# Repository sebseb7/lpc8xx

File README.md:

lpc8xx_template
===============

template project with makefile, flash script and eval board.

- - - 

####lpc812 features:

* Cortex-M0+ Core
* 30 Mhz
* 16kb flash (lpc811: 8kb)
* 4kb RAM (lpc811: 2kb)
* USART Bootloader and SerialWireDebugging ( make debug )
* ROM drivers for USART, i2c and power profiles
* 14 hihgly configurable GPIO Pins (you can connect UART, I2C and SPI to any pin)
* 3 * USART , 2 * SPI , 1 * I2C
* internal RC with 1% accuracy
* while(1); @ 30 Mhz ==> 5.5mA

- - -

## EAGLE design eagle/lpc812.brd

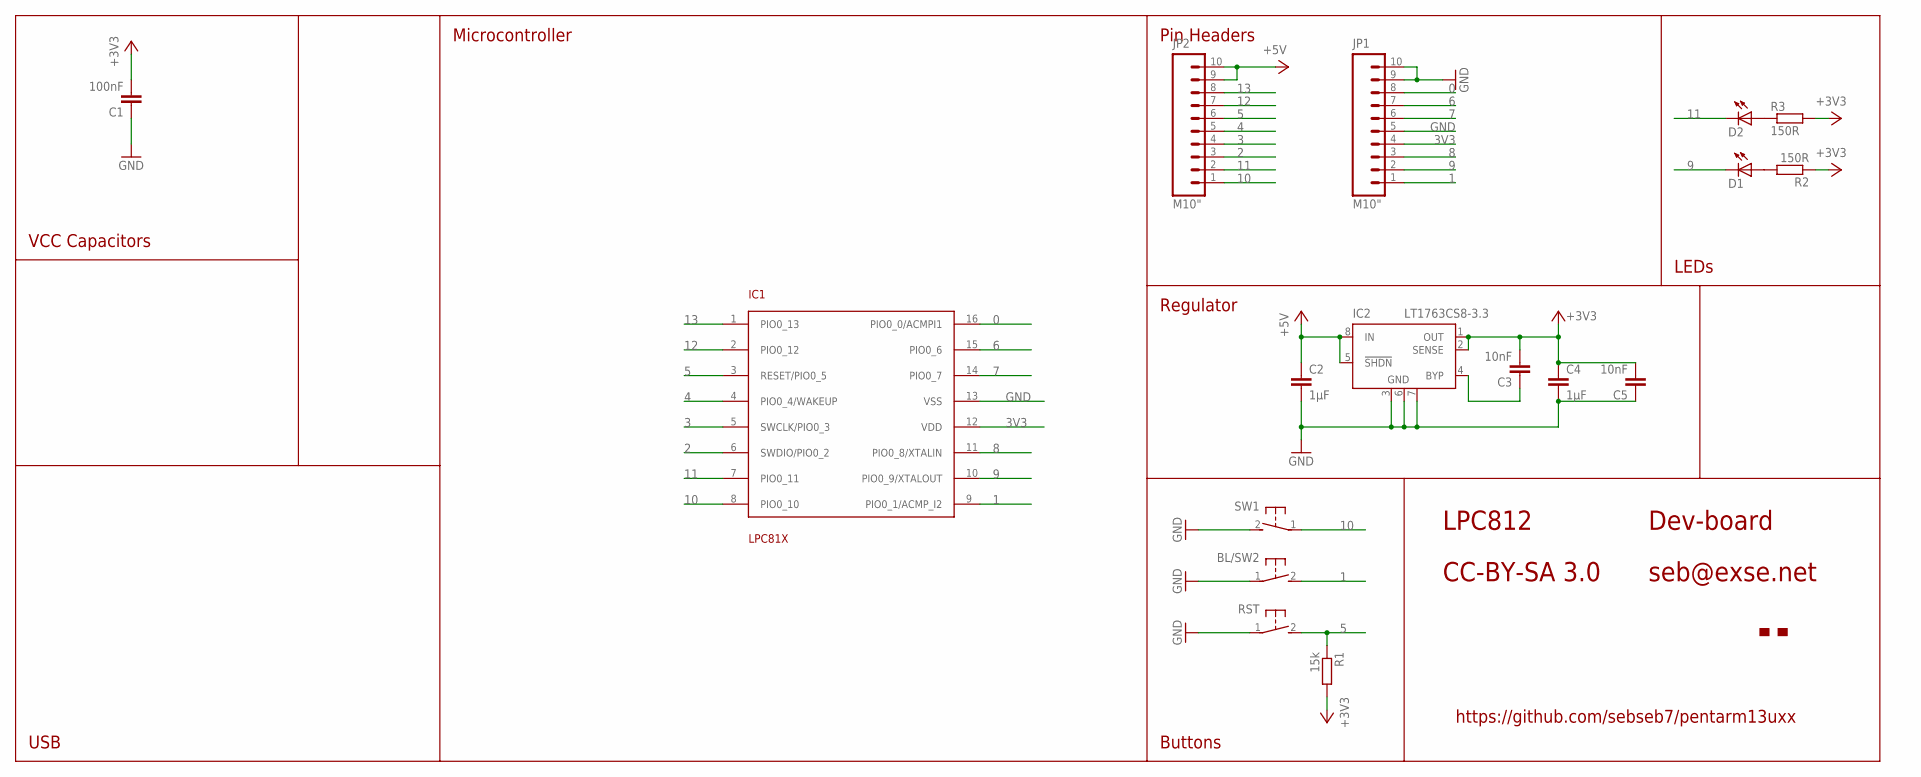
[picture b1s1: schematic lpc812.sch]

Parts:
BL/SW2: SWITCH_MCTAEF
C1: 100nF; C0402
C2, C4: 1µF; 0805
C3, C5: 10nF; C0402
D1, D2: LEDCHIPLED_0805; CHIPLED_0805
IC1: LPC81X; TSSOP16
IC2: LT1763CS8-3.3; SOIC8
JP1, JP2: M10"; 1X10
R1: 15k; R0402
R2, R3: 150R; R0402
RST: SWITCH_MCTAEF
SW1: SWITCH_MCTAEF
U$1: MAKE-DD_LOGO'PROMPT'; MAKE-DD_LOGO_PROMPT

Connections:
0: IC1.16 (PIO0_0/ACMPI1), JP1.8
1: BL/SW2.2, IC1.9 (PIO0_1/ACMP_I2), JP1.1
2: IC1.6 (SWDIO/PIO0_2), JP2.3
3: IC1.5 (SWCLK/PIO0_3), JP2.4
3V3: C1.2, C3.2, C4.1, C5.2, IC1.12 (VDD), IC2.1 (OUT), IC2.2 (SENSE), JP1.4, R1.2, R2.1, R3.2
4: IC1.4 (PIO0_4/WAKEUP), JP2.5
5: IC1.3 (RESET/PIO0_5), JP2.6, R1.1, RST.2
6: IC1.15 (PIO0_6), JP1.7
7: IC1.14 (PIO0_7), JP1.6
8: IC1.11 (PIO0_8/XTALIN), JP1.3
9: D1.C, IC1.10 (PIO0_9/XTALOUT), JP1.2
10: IC1.8 (PIO0_10), JP2.1, SW1.1
11: D2.C, IC1.7 (PIO0_11), JP2.2
12: IC1.2 (PIO0_12), JP2.7
13: IC1.1 (PIO0_13), JP2.8
+5V: C2.1, IC2.5 (!SHDN), IC2.8 (IN), JP2.9, JP2.10
GND: BL/SW2.1, C1.1, C2.2, C4.2, C5.1, IC1.13 (VSS), IC2.3 (GND), IC2.6 (GND), IC2.7 (GND), JP1.5, JP1.9, JP1.10, RST.1, SW1.2
unnamed: C3.1, IC2.4 (BYP)
unnamed: D1.A, R2.2
unnamed: D2.A, R3.1

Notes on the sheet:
Pin Headers
Regulator
Buttons
LEDs
Microcontroller
VCC Capacitors
USB
CC-BY-SA 3.0
seb@exse.net
LPC812
Dev-board
https://github.com/sebseb7/pentarm13uxx

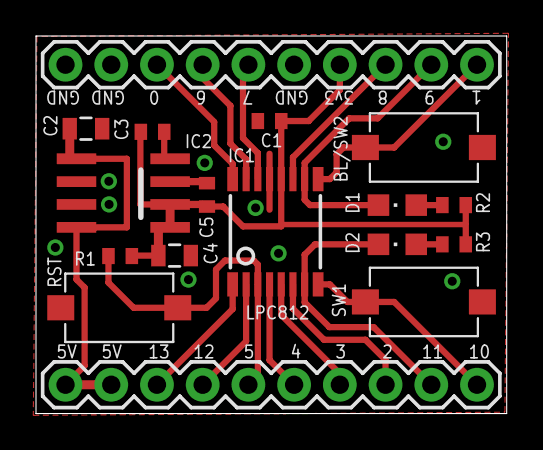
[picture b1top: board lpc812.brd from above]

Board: 2 copper layers, 26.1 x 21.0 mm, 18 parts (1 on the bottom side), 20 nets.

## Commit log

2013-03-06 ignore
2013-03-06 correct memory sizes
2013-03-06 flags
2013-03-06 ret type
2013-03-06 bss symbols
2013-03-06 switch tool
2013-03-18 updated from example
2013-03-18 fixed linker script
2013-03-18 simple blink example
2013-03-18 added flash target
2013-03-18 typos
2013-03-19 added test board
2013-03-19 startup code size optimization, crp disabled
2013-03-19 removed uncessessary stuff
2013-03-19 moved sysinit to .after_vectors
2013-03-19 minor optimization
2013-03-19 use .d files for dep tracking of headers
2013-03-19 rename a file & moved all temporary compilation files to .bin directory
2013-03-19 minor adjustments
2013-03-19 small fix
2013-03-20 added patched lpc21isp
2013-03-20 added switch matrix tool
2013-03-20 added python script for uart isp flashing
2013-03-20 final touches
2013-03-20 typo & elimenate make clean waring
2013-03-21 added 810,811 support
2013-03-21 added gdb makefile target
2013-04-27 cmsis 3.2
2013-09-04 make the eval board run at 30Mhz and let LEDs test-blink at 1Hz
2013-09-04 pwr consumtion
2013-09-04 revert
2013-09-04 value lables
2014-12-10 use small multiply
2015-04-06 gcc 4.9 2015q1
2015-04-06 merge
2015-04-06 readd

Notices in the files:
parts and their libraries:
SparkFun-Connectors: Licensing: CC v3.0 Share-Alike You are welcome to use this library for commercial purposes.
